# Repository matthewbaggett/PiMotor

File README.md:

PiMotor
=======

Raspberry Pi DC motor controller

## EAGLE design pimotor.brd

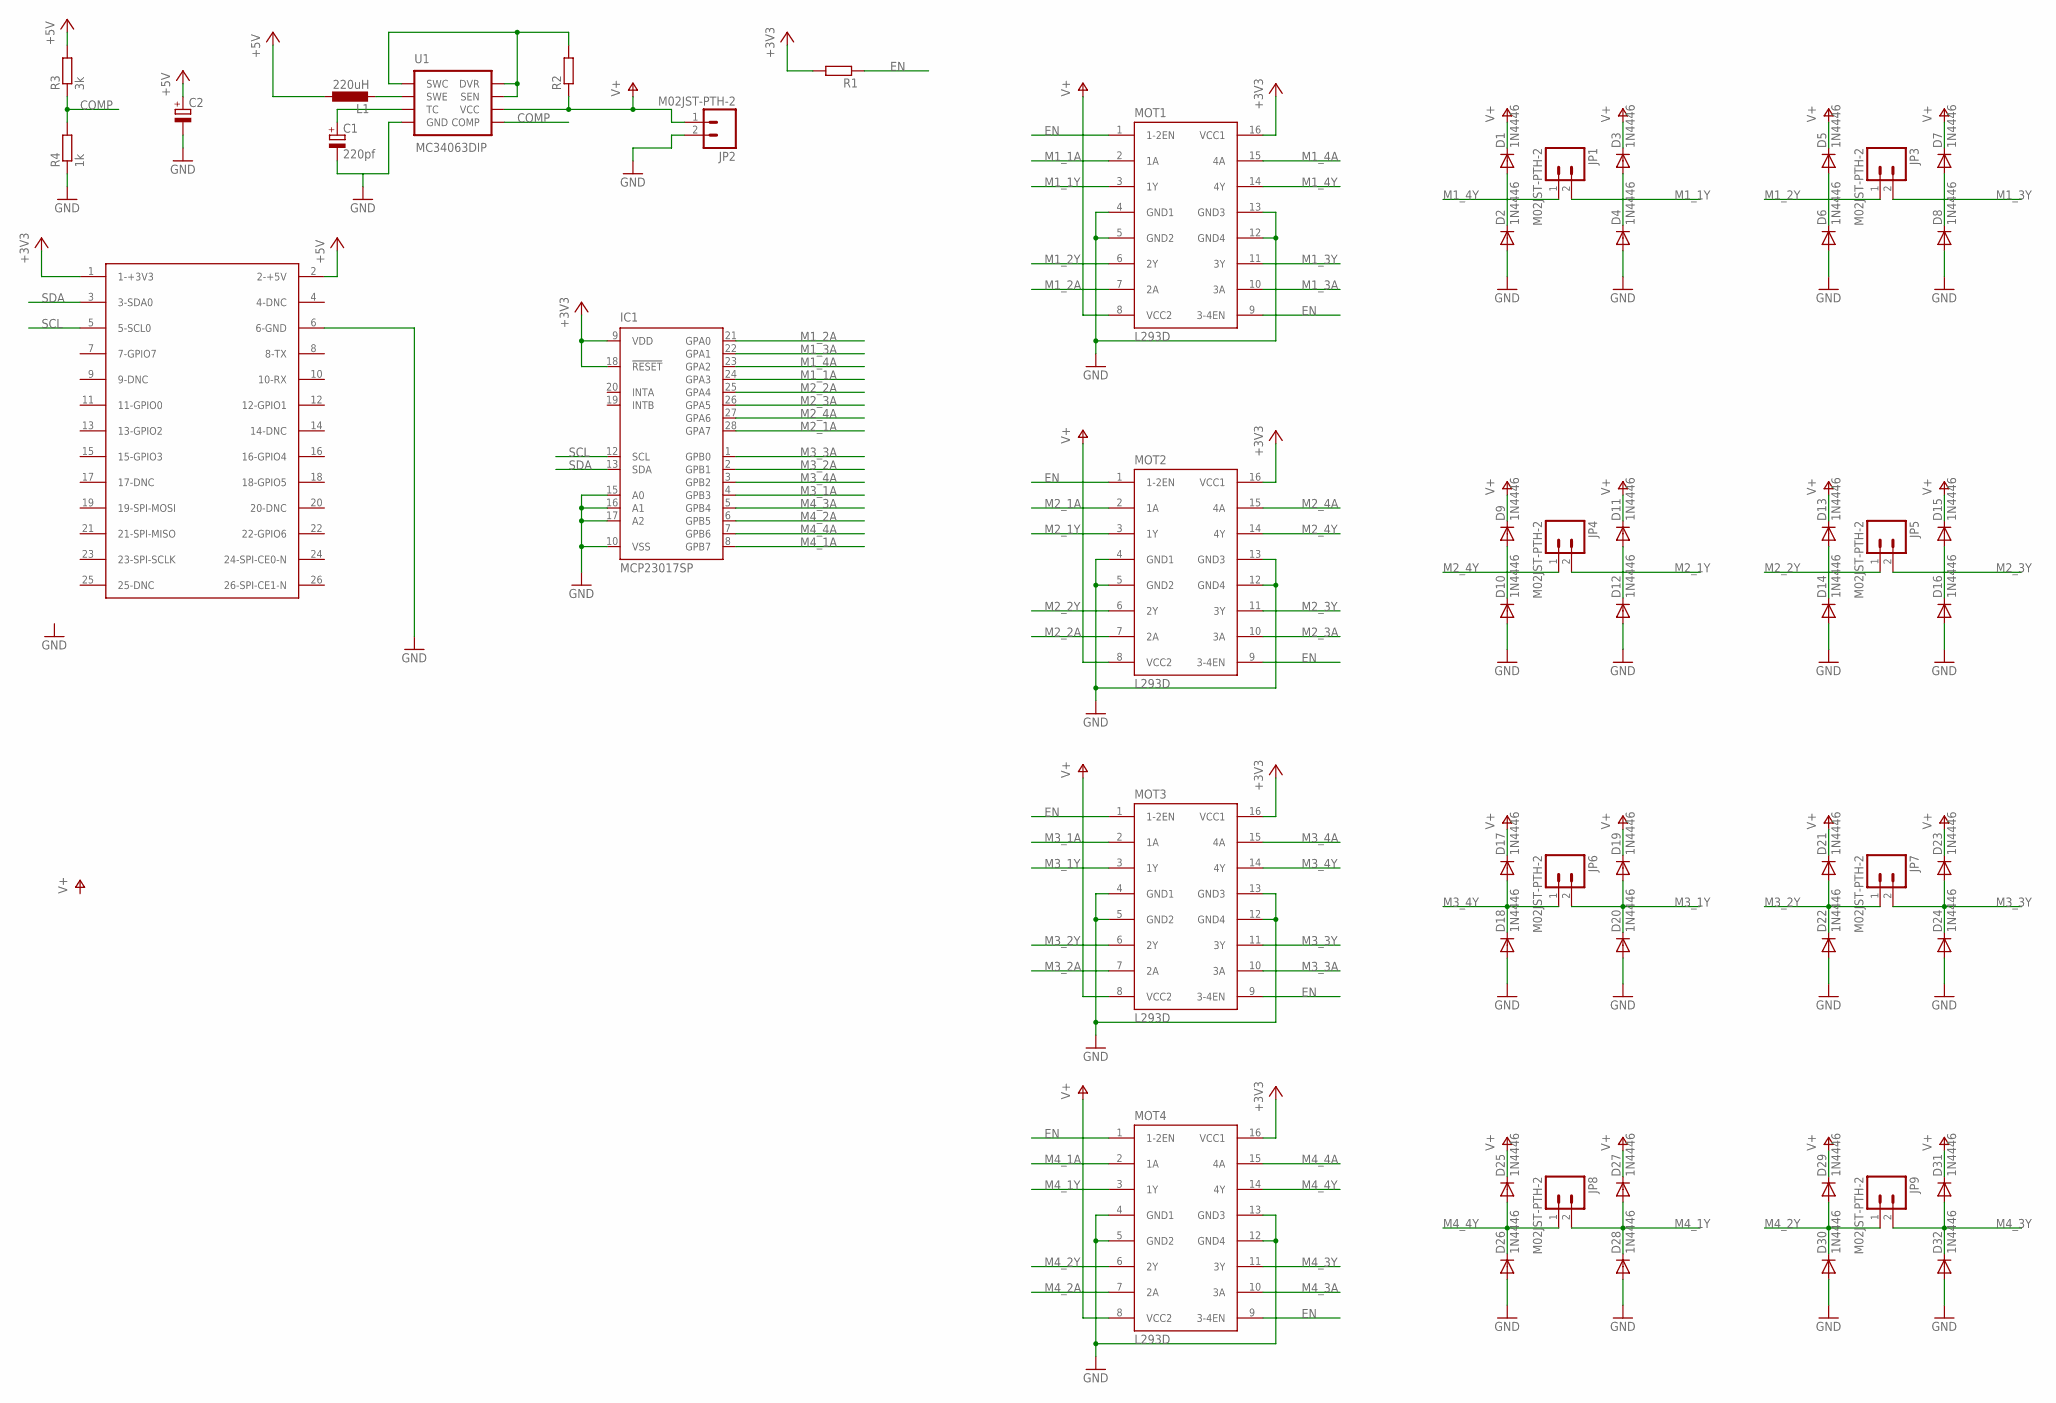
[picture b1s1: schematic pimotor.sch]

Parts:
C1: 220pf; E3,5-8
C2: CPOL-EUE3.5-8; E3,5-8
D1, D2, D3, D4, D5, D6, D7, D8, D9, D10, D11, D12, D13, D14, D15, D16, D17, D18, D19, D20, D21, D22, D23, D24, D25, D26, D27, D28, D29, D30, D31, D32: 1N4446; DO35-10
IC1: MCP23017SP; DIL28-3
JP1, JP2, JP3, JP4, JP5, JP6, JP7, JP8, JP9: M02JST-PTH-2; JST-2-PTH
L1: 220uH; 0204/7
MOT1, MOT2, MOT3, MOT4: L293D; DIL16
R1, R2: R-EU_0204/7; 0204/7
R3: 3k; 0204/7
R4: 1k; 0204/7
U1: MC34063DIP; DIP-08
U$1: RASPBERRY-PI

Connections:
+3V3: IC1.9 (VDD), IC1.18 (!RESET), MOT1.16 (VCC1), MOT2.16 (VCC1), MOT3.16 (VCC1), MOT4.16 (VCC1), R1.2, U$1.1 (1-+3V3)
+5V: C2.+, L1.1, R3.2, U$1.2 (2-+5V)
COMP: R3.1, R4.2, U1.5 (COMP)
EN: MOT1.1 (1-2EN), MOT1.9 (3-4EN), MOT2.1 (1-2EN), MOT2.9 (3-4EN), MOT3.1 (1-2EN), MOT3.9 (3-4EN), MOT4.1 (1-2EN), MOT4.9 (3-4EN), R1.1
GND: C1.-, C2.-, D2.A, D4.A, D6.A, D8.A, D10.A, D12.A, D14.A, D16.A, D18.A, D20.A, D22.A, D24.A, D26.A, D28.A, D30.A, D32.A, IC1.10 (VSS), IC1.15 (A0), IC1.16 (A1), IC1.17 (A2), JP2.2, MOT1.4 (GND1), MOT1.5 (GND2), MOT1.12 (GND4), MOT1.13 (GND3), MOT2.4 (GND1), MOT2.5 (GND2), MOT2.12 (GND4), MOT2.13 (GND3), MOT3.4 (GND1), MOT3.5 (GND2), MOT3.12 (GND4), MOT3.13 (GND3), MOT4.4 (GND1), MOT4.5 (GND2), MOT4.12 (GND4), MOT4.13 (GND3), R4.1, U1.4 (GND), U$1.6 (6-GND)
M1_1A: IC1.24 (GPA3), MOT1.2 (1A)
M1_1Y: D3.A, D4.C, JP1.2, MOT1.3 (1Y)
M1_2A: IC1.21 (GPA0), MOT1.7 (2A)
M1_2Y: D5.A, D6.C, JP3.1, MOT1.6 (2Y)
M1_3A: IC1.22 (GPA1), MOT1.10 (3A)
M1_3Y: D7.A, D8.C, JP3.2, MOT1.11 (3Y)
M1_4A: IC1.23 (GPA2), MOT1.15 (4A)
M1_4Y: D1.A, D2.C, JP1.1, MOT1.14 (4Y)
M2_1A: IC1.28 (GPA7), MOT2.2 (1A)
M2_1Y: D11.A, D12.C, JP4.2, MOT2.3 (1Y)
M2_2A: IC1.25 (GPA4), MOT2.7 (2A)
M2_2Y: D13.A, D14.C, JP5.1, MOT2.6 (2Y)
M2_3A: IC1.26 (GPA5), MOT2.10 (3A)
M2_3Y: D15.A, D16.C, JP5.2, MOT2.11 (3Y)
M2_4A: IC1.27 (GPA6), MOT2.15 (4A)
M2_4Y: D9.A, D10.C, JP4.1, MOT2.14 (4Y)
M3_1A: IC1.4 (GPB3), MOT3.2 (1A)
M3_1Y: D19.A, D20.C, JP6.2, MOT3.3 (1Y)
M3_2A: IC1.2 (GPB1), MOT3.7 (2A)
M3_2Y: D21.A, D22.C, JP7.1, MOT3.6 (2Y)
M3_3A: IC1.1 (GPB0), MOT3.10 (3A)
M3_3Y: D23.A, D24.C, JP7.2, MOT3.11 (3Y)
M3_4A: IC1.3 (GPB2), MOT3.15 (4A)
M3_4Y: D17.A, D18.C, JP6.1, MOT3.14 (4Y)
M4_1A: IC1.8 (GPB7), MOT4.2 (1A)
M4_1Y: D27.A, D28.C, JP8.2, MOT4.3 (1Y)
M4_2A: IC1.6 (GPB5), MOT4.7 (2A)
M4_2Y: D29.A, D30.C, JP9.1, MOT4.6 (2Y)
M4_3A: IC1.5 (GPB4), MOT4.10 (3A)
M4_3Y: D31.A, D32.C, JP9.2, MOT4.11 (3Y)
M4_4A: IC1.7 (GPB6), MOT4.15 (4A)
M4_4Y: D25.A, D26.C, JP8.1, MOT4.14 (4Y)
unnamed: L1.2, U1.2 (SWE)
unnamed: R2.2, U1.1 (SWC), U1.7 (SEN), U1.8 (DVR)
unnamed: C1.+, U1.3 (TC)
SCL: IC1.12 (SCL), U$1.5 (5-SCL0)
SDA: IC1.13 (SDA), U$1.3 (3-SDA0)
V+: D1.C, D3.C, D5.C, D7.C, D9.C, D11.C, D13.C, D15.C, D17.C, D19.C, D21.C, D23.C, D25.C, D27.C, D29.C, D31.C, JP2.1, MOT1.8 (VCC2), MOT2.8 (VCC2), MOT3.8 (VCC2), MOT4.8 (VCC2), R2.1, U1.6 (VCC)

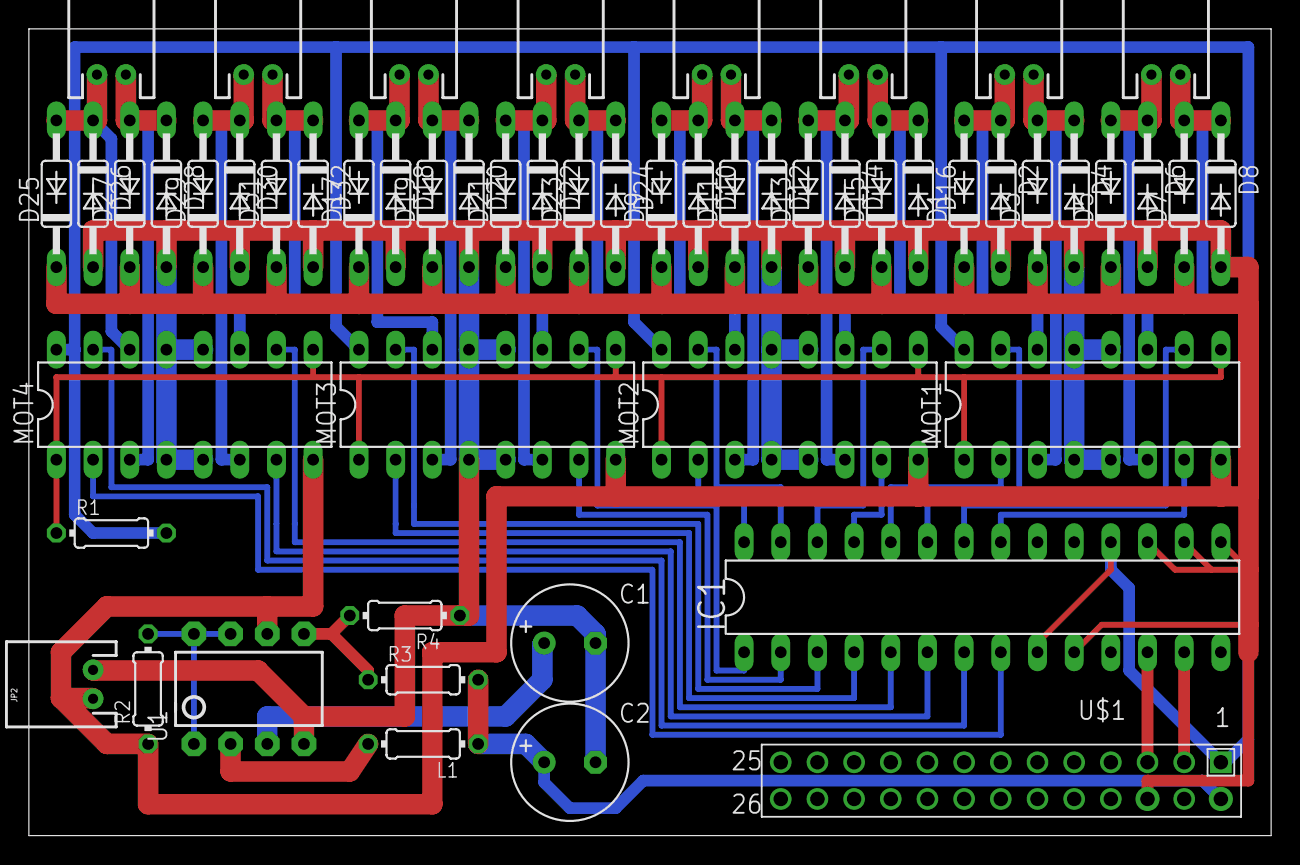
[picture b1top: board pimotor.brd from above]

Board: 2 copper layers, 86.0 x 55.9 mm, 55 parts (0 on the bottom side), 43 nets.

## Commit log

2014-04-02 PiMotor initial commit

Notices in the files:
parts and their libraries:
SparkFun-Connectors: Licensing: Creative Commons ShareAlike 4.0 International - https://creativecommons.org/licenses/by-sa/4.0
